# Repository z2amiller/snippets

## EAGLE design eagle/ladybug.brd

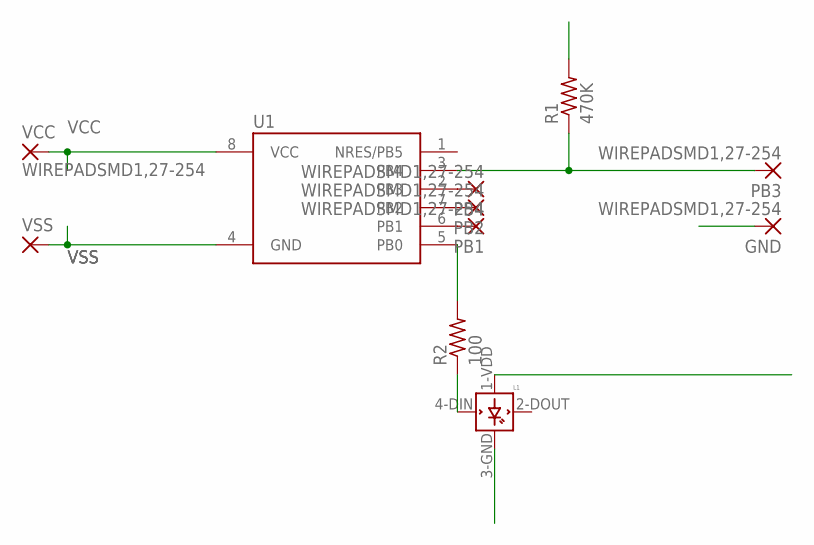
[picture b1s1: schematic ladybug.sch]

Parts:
GND: WIREPADSMD1,27-254; SMD1,27-2,54
L1: WS2812B
PB1, PB2, PB3, PB4: WIREPADSMD1,27-254; SMD1,27-2,54
R1: 470K; M1206
R2: 100; M1206
U1: ATTINY85-20S; SOIC8_EIAJ_208MIL
VCC: WIREPADSMD1,27-254; SMD1,27-2,54
VSS: WIREPADSMD1,27-254; SMD1,27-2,54

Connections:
unnamed: R2.2, U1.5 (PB0)
unnamed: L1.4-DIN (DIN), R2.1
unnamed: PB4.1, U1.2 (PB3)
unnamed: PB1.1, U1.6 (PB1)
unnamed: PB2.1, U1.7 (PB2)
PB3: PB3.1, R1.1, U1.3 (PB4)
VCC: L1.1-VDD (VDD), R1.2, U1.8 (VCC), VCC.1
VSS: GND.1, L1.3-GND (GND), U1.4 (GND), VSS.1

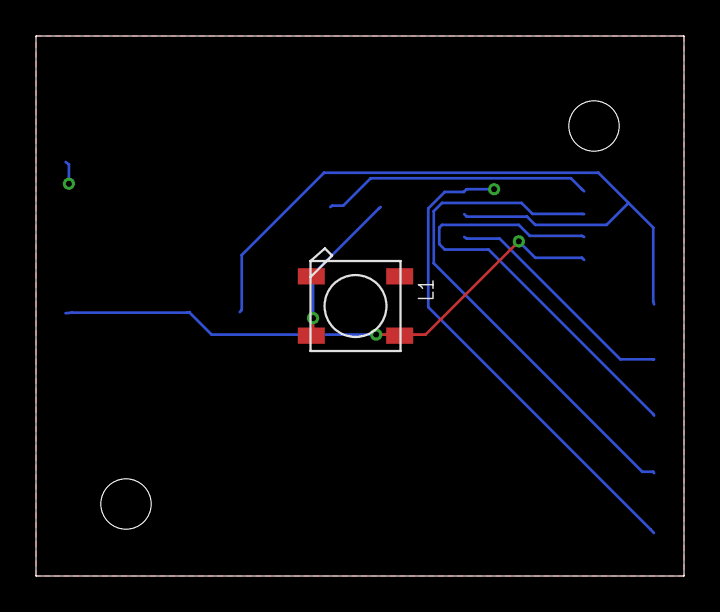
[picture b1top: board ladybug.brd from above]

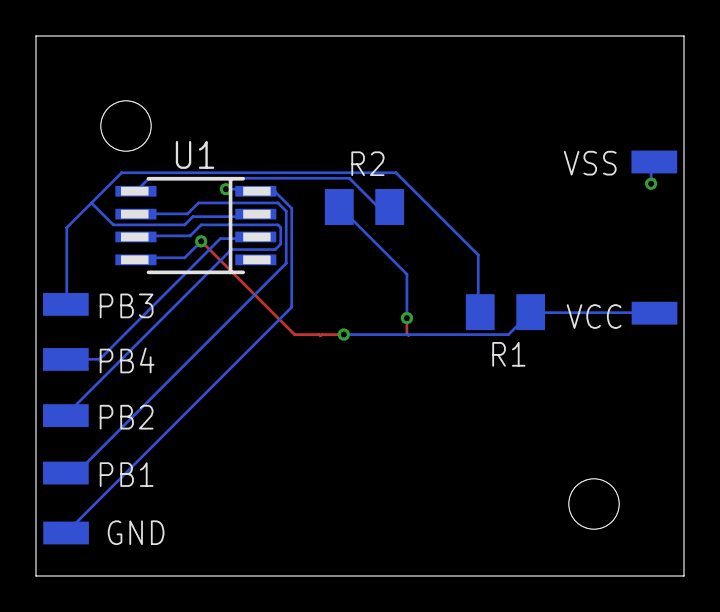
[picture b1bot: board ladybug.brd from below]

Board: 2 copper layers, 36.0 x 30.0 mm, 11 parts (10 on the bottom side), 8 nets.

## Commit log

2015-08-05 Initial checkin of mFi "code" to snippets.
2015-08-05 Remove README header.
2015-08-06 Initial commit of ladybug board.
2015-08-07 Fixed ground plane and drill holes.
2015-08-09 Some prometheus support and config files.
2015-08-09 Change label of scraped nodes.
2015-08-12 Send sensor data to prometheus from an esp8266
2015-09-21 Add bmp180 board
2015-09-21 KiCad files for PrometheusSensor
2015-09-21 Centralize PrometheusSensor code
2015-09-21 Clean up comments and formatting.
2015-10-17 Move ladybug files to dedicated repository.
2015-10-17 Moved sensor to a dedicated repository.
2015-10-31 Quickie breakout for sot-23 and sot-23-5.
2015-11-01 8 x temperature sensor for esp8266.
2015-11-02 Rearrange board to fit properly in Hammond 1551L.
2015-11-02 Fix board outline - try, try again.
2015-11-16 Boost converter board based on XC9401.
2015-11-16 Simple breakout for passives.
2015-11-24 Some test code for octotemp using the TI128d818.
2015-11-24 Some quick code cleanups.
2015-11-24 Fix programming header and reset.
2015-12-17 Octotemp board with 2 1x8 pin JST connectors.
2015-12-17 Fixed silkscreening.
2015-12-17 Added name/version silkscreening.
2016-02-21 Use prometheus client to send messages.
2016-02-22 A mostly-working OctoTemp
2016-02-22 Use the new MapMetric
2016-02-22 Fix OctoTemp, set up to use esp8266 2.0.1-rc2
2016-02-22 TODO -> Done
2016-02-22 Added a constraint on tempC
2016-02-23 Use the new adc128d818 library.
2016-02-29 Increased the drill sizes of the JST connectors
2016-02-29 Initialize the wire library explicitly.
2016-03-20 Create a breakout for the BME280
2016-03-20 Why didn't I make this sot23-6 in the first place?
2016-03-20 Larger pads, better soldermask
2016-04-11 ESP8266 neopixel driver in a Hammond 1551H box.
2016-04-11 Fix some silkscreens.
2016-04-22 Replace oval drills with edgecut slots for OSHPark
2016-04-22 Increase 5v zone size
2016-05-08 Don't use GPIO10 which apparently is reserved.
2016-07-09 Use MCP1702 for regulator, use reflow sized pads.
2016-07-09 No gerbers
